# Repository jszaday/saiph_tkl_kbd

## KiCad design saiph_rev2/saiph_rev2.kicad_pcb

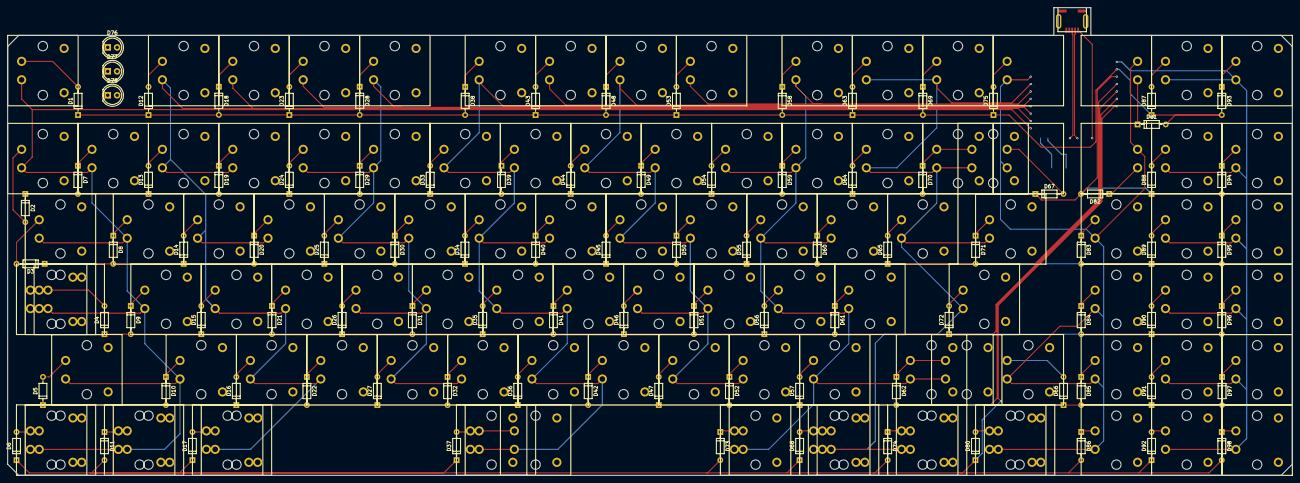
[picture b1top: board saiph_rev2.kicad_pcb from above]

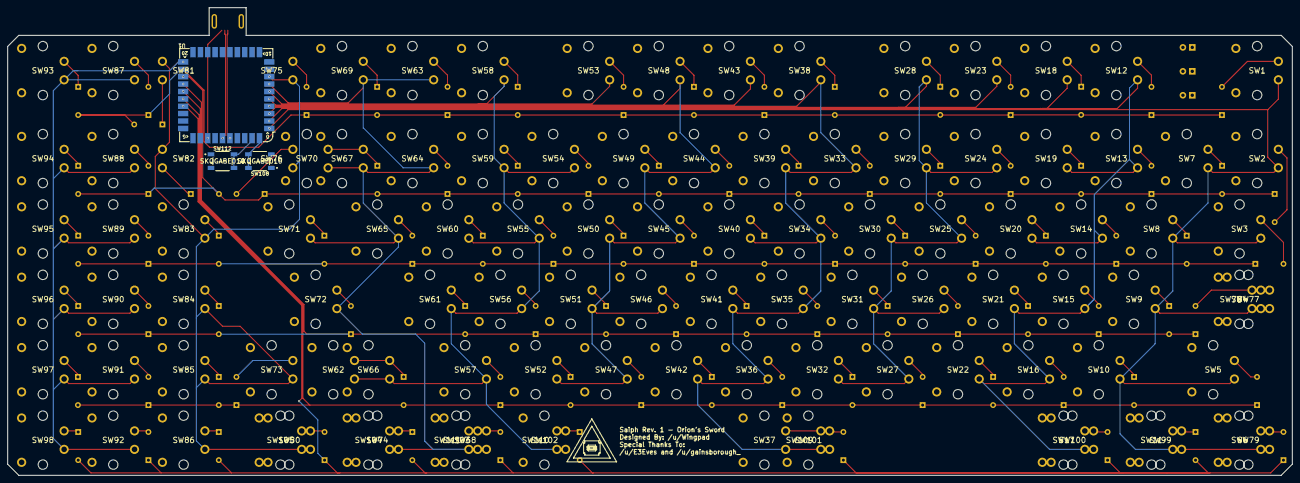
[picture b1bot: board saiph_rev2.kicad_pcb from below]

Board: 2 copper layers, 347.7 x 126.6 mm, 210 parts (4 on the bottom side), 115 nets.

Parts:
D1, D2, D3, D4, D5, D6, D7, D8, D9, D10, D11, D12, D13, D14, D15, D16, D17, D18, D19, D20, D21, D22, D23, D24, D25, D26, D27, D28, D29, D30, D31, D32, D33, D34, D35, D36, D37, D38, D39, D40, D41, D42, D43, D44, D45, D46, D47, D48, D49, D50, D51, D52, D53, D54, D55, D56, D57, D58, D59, D60, D61, D62, D63, D64, D65, D66, D67, D68, D69, D70, D71, D72, D73, D74, D75, D80, D81, D82, D83, D84, D85, D86, D87, D88, D89, D90, D91, D92, D93, D94, D95, D96, D97, D98: D; D_DO-35_SOD27_P7.62mm_Horizontal
D76, D77, D78: LED; LED_D5.0mm
J1: USB_mini_micro_B; USB_miniB_hirose_5S8
M1: MISC; illuminalpsi
SW1, SW2, SW3, SW4, SW5, SW6, SW7, SW8, SW9, SW10, SW11, SW12, SW13, SW14, SW15, SW16, SW17, SW18, SW19, SW20, SW21, SW22, SW23, SW24, SW25, SW26, SW27, SW28, SW29, SW30, SW31, SW32, SW33, SW34, SW35, SW36, SW37, SW38, SW39, SW40, SW41, SW42, SW43, SW44, SW45, SW46, SW47, SW48, SW49, SW50, SW51, SW52, SW53, SW54, SW55, SW56, SW57, SW58, SW59, SW60, SW61, SW62, SW63, SW64, SW65, SW66, SW67, SW68, SW69, SW70, SW71, SW72, SW73, SW74, SW77, SW79, SW80, SW83, SW84, SW85, SW86, SW87, SW88, SW89, SW90, SW91, SW92, SW93, SW94, SW95, SW96, SW97, SW98, SW99, SW100, SW101, SW102, SW103, SW104, SW105: SW_PUSH; ALPS_PLATE
SW75, SW76, SW81, SW82: SW_PUSH; ALPS_PLATE_SPRING_PARTIAL
SW78, SW109, SW110, SW111: SW_PUSH; ALPS_PLATE_PLATE
SW108, SW112: SKQGABE010; Switch_ALPS_SKQGABE010
U1: RP2040_Stamp; RP2040_Stamp_SMD

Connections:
+5V: J1.1 (VUSB), U1.33 (5V)
/BOOTSEL: SW108.2, SW108.4, U1.40 (BOOTSEL)
/C0: SW1.1, SW2.1, SW3.1, SW4.1, SW5.1, SW6.1, SW7.1, SW8.1, SW9.1, SW10.1, SW11.1, SW77.1, SW78.1, SW79.1, SW99.1, U1.1 (GPIO0)
/C1: SW12.1, SW13.1, SW14.1, SW15.1, SW16.1, SW17.1, SW18.1, SW19.1, SW20.1, SW21.1, SW22.1, SW100.1, U1.2 (GPIO1)
/C2: SW23.1, SW24.1, SW25.1, SW26.1, SW27.1, SW28.1, SW29.1, SW30.1, SW31.1, SW32.1, U1.3 (GPIO2)
/C3: SW33.1, SW34.1, SW35.1, SW36.1, SW37.1, SW38.1, SW39.1, SW40.1, SW41.1, SW42.1, SW101.1, SW109.1, U1.4 (GPIO3)
/C4: SW43.1, SW44.1, SW45.1, SW46.1, SW47.1, SW48.1, SW49.1, SW50.1, SW51.1, SW52.1, U1.5 (GPIO4)
/C5: SW53.1, SW54.1, SW55.1, SW56.1, SW57.1, SW58.1, SW59.1, SW60.1, SW61.1, SW62.1, SW66.1, SW102.1, SW110.1, U1.6 (GPIO5)
/C6: SW63.1, SW64.1, SW65.1, SW67.1, SW68.1, SW69.1, SW70.1, SW71.1, SW72.1, SW74.1, SW103.1, SW104.1, SW111.1, U1.7 (GPIO6)
/C7: SW73.1, SW75.1, SW76.1, SW80.1, SW81.1, SW82.1, SW83.1, SW84.1, SW85.1, SW86.1, SW105.1, U1.8 (GPIO7)
/C8: SW87.1, SW88.1, SW89.1, SW90.1, SW91.1, SW92.1, SW93.1, SW94.1, SW95.1, SW96.1, SW97.1, SW98.1, U1.21 (GPIO20)
/NRST: SW112.2, SW112.4, U1.39 (~RESET)
/R0: D1.1 (K), D12.1 (K), D18.2 (A), D23.1 (K), D28.2 (A), D38.2 (A), D43.1 (K), D48.2 (A), D53.1 (K), D58.2 (A), D63.1 (K), D69.2 (A), D75.1 (K), D81.2 (A), D87.1 (K), D93.2 (A), U1.22 (GPIO21)
/R1: D2.1 (K), D7.2 (A), D13.1 (K), D19.2 (A), D24.1 (K), D29.2 (A), D33.1 (K), D39.2 (A), D44.1 (K), D49.2 (A), D54.1 (K), D59.2 (A), D64.1 (K), D67.1 (K), D70.2 (A), D82.2 (A), D88.1 (K), D94.2 (A), U1.23 (GPIO22)
/R2: D3.1 (K), D8.2 (A), D14.1 (K), D20.2 (A), D25.1 (K), D30.2 (A), D34.1 (K), D40.2 (A), D45.1 (K), D50.2 (A), D55.1 (K), D60.2 (A), D65.1 (K), D71.2 (A), D83.2 (A), D89.1 (K), D95.2 (A), U1.24 (GPIO23)
/R3: D4.1 (K), D9.2 (A), D15.1 (K), D21.2 (A), D26.1 (K), D31.2 (A), D35.1 (K), D41.2 (A), D46.1 (K), D51.2 (A), D56.1 (K), D61.2 (A), D72.1 (K), D84.2 (A), D90.1 (K), D96.2 (A), U1.25 (GPIO24)
/R4: D5.1 (K), D10.2 (A), D16.1 (K), D22.2 (A), D27.1 (K), D32.2 (A), D36.1 (K), D42.2 (A), D47.1 (K), D52.2 (A), D57.1 (K), D62.2 (A), D66.1 (K), D85.2 (A), D91.1 (K), D97.2 (A), U1.26 (GPIO25)
/R5: D6.1 (K), D11.2 (A), D17.1 (K), D37.1 (K), D68.1 (K), D73.2 (A), D74.2 (A), D80.1 (K), D86.2 (A), D92.1 (K), D98.2 (A), U1.27 (GPIO26)
/USB_D+: J1.3 (D+), U1.36 (USB_D+)
/USB_D-: J1.2 (D-), U1.35 (USB_D-)
GND: J1.5 (GND), J1.6 (SHIELD), SW108.1, SW108.3, SW112.1, SW112.3, U1.31 (GND)
unnamed: D1.2 (A), SW1.2
unnamed: D2.2 (A), SW2.2
unnamed: D3.2 (A), SW3.2
unnamed: D4.2 (A), SW4.2, SW77.2, SW78.2
unnamed: D5.2 (A), SW5.2
unnamed: D6.2 (A), SW6.2, SW79.2
unnamed: D7.1 (K), SW7.2
unnamed: D8.1 (K), SW8.2
unnamed: D9.1 (K), SW9.2
unnamed: D10.1 (K), SW10.2
unnamed: D11.1 (K), SW11.2, SW99.2
unnamed: D12.2 (A), SW12.2
unnamed: D13.2 (A), SW13.2
unnamed: D14.2 (A), SW14.2
unnamed: D15.2 (A), SW15.2
unnamed: D16.2 (A), SW16.2
unnamed: D17.2 (A), SW17.2, SW100.2
unnamed: D18.1 (K), SW18.2
unnamed: D19.1 (K), SW19.2
unnamed: D20.1 (K), SW20.2
unnamed: D21.1 (K), SW21.2
unnamed: D22.1 (K), SW22.2
unnamed: D23.2 (A), SW23.2
unnamed: D24.2 (A), SW24.2
unnamed: D25.2 (A), SW25.2
unnamed: D26.2 (A), SW26.2
unnamed: D27.2 (A), SW27.2
unnamed: D28.1 (K), SW28.2
unnamed: D29.1 (K), SW29.2
unnamed: D30.1 (K), SW30.2
unnamed: D31.1 (K), SW31.2
unnamed: D32.1 (K), SW32.2
unnamed: D33.2 (A), SW33.2
unnamed: D34.2 (A), SW34.2
unnamed: D35.2 (A), SW35.2
unnamed: D36.2 (A), SW36.2
unnamed: D37.2 (A), SW37.2, SW101.2, SW109.2
unnamed: D38.1 (K), SW38.2
unnamed: D39.1 (K), SW39.2
unnamed: D40.1 (K), SW40.2
unnamed: D41.1 (K), SW41.2
unnamed: D42.1 (K), SW42.2
unnamed: D43.2 (A), SW43.2
unnamed: D44.2 (A), SW44.2
unnamed: D45.2 (A), SW45.2
unnamed: D46.2 (A), SW46.2
unnamed: D47.2 (A), SW47.2
unnamed: D48.1 (K), SW48.2
unnamed: D49.1 (K), SW49.2
unnamed: D50.1 (K), SW50.2
unnamed: D51.1 (K), SW51.2
unnamed: D52.1 (K), SW52.2
unnamed: D53.2 (A), SW53.2
unnamed: D54.2 (A), SW54.2
unnamed: D55.2 (A), SW55.2
unnamed: D56.2 (A), SW56.2
unnamed: D57.2 (A), SW57.2
unnamed: D58.1 (K), SW58.2
unnamed: D59.1 (K), SW59.2
unnamed: D60.1 (K), SW60.2
unnamed: D61.1 (K), SW61.2
unnamed: D62.1 (K), SW62.2, SW66.2
unnamed: D63.2 (A), SW63.2
unnamed: D64.2 (A), SW64.2
unnamed: D65.2 (A), SW65.2
unnamed: D66.2 (A), SW73.2
unnamed: D67.2 (A), SW76.2
unnamed: D68.2 (A), SW68.2, SW103.2, SW111.2
unnamed: D69.1 (K), SW69.2
unnamed: D70.1 (K), SW67.2, SW70.2
unnamed: D71.1 (K), SW71.2
unnamed: D72.2 (A), SW72.2
unnamed: D73.1 (K), SW102.2, SW110.2
unnamed: D74.1 (K), SW74.2, SW104.2
unnamed: D75.2 (A), SW75.2
unnamed: D80.2 (A), SW80.2, SW105.2
unnamed: D81.1 (K), SW81.2
unnamed: D82.1 (K), SW82.2
unnamed: D83.1 (K), SW83.2
unnamed: D84.1 (K), SW84.2
unnamed: D85.1 (K), SW85.2
unnamed: D86.1 (K), SW86.2
unnamed: D87.2 (A), SW87.2
unnamed: D88.2 (A), SW88.2
unnamed: D89.2 (A), SW89.2
unnamed: D90.2 (A), SW90.2
unnamed: D91.2 (A), SW91.2
unnamed: D92.2 (A), SW92.2
unnamed: D93.1 (K), SW93.2
unnamed: D94.1 (K), SW94.2
unnamed: D95.1 (K), SW95.2
unnamed: D96.1 (K), SW96.2
unnamed: D97.1 (K), SW97.2
unnamed: D98.1 (K), SW98.2

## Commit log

2023-04-19 initial commit.
2023-04-19 add plates
2023-04-20 add pro micro and usb
2023-04-20 add promicro
2023-04-23 rotate diodes
2023-04-23 change footprints to attempt better fit
2023-05-02 place rp2040 stamp and buttons; start planning routing
2023-05-02 remove traces.
2023-05-05 add usb traces
2023-05-05 route cols/rows; main arteries
2023-05-05 place r4 diodes
2023-05-06 route more diodes
2023-05-06 route more diodes n' stuff (ii)
2023-05-06 routing pretty much done.
2023-05-07 Add submodule and ignore files.
